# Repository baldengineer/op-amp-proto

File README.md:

## Op Amp board for Prototyping and testing Op Amps
This board characterizes op amps in an SOIC-8 breakout board. The bottom layer is solid copper. The top has copper guard bands. There are solder jumps to connect the copper pours whatever pin is GND on the SOIC.

Turns out, if you bend the leads, version 1 can fit a DIP.

The "top" and "bottom" 2.54 mm holes are intended for power rails.

## Featured on ...
See the board in action in this element14 Present's Workbench Wednesdays video on [Slew Rate versus Rise Time](https://community.element14.com/challenges-projects/element14-presents/workbenchwednesdays/w/documents/27980/workbench-wednesdays-67-slew-rate-vs-rise-time-measurements-for-op-amps "element14 Community").

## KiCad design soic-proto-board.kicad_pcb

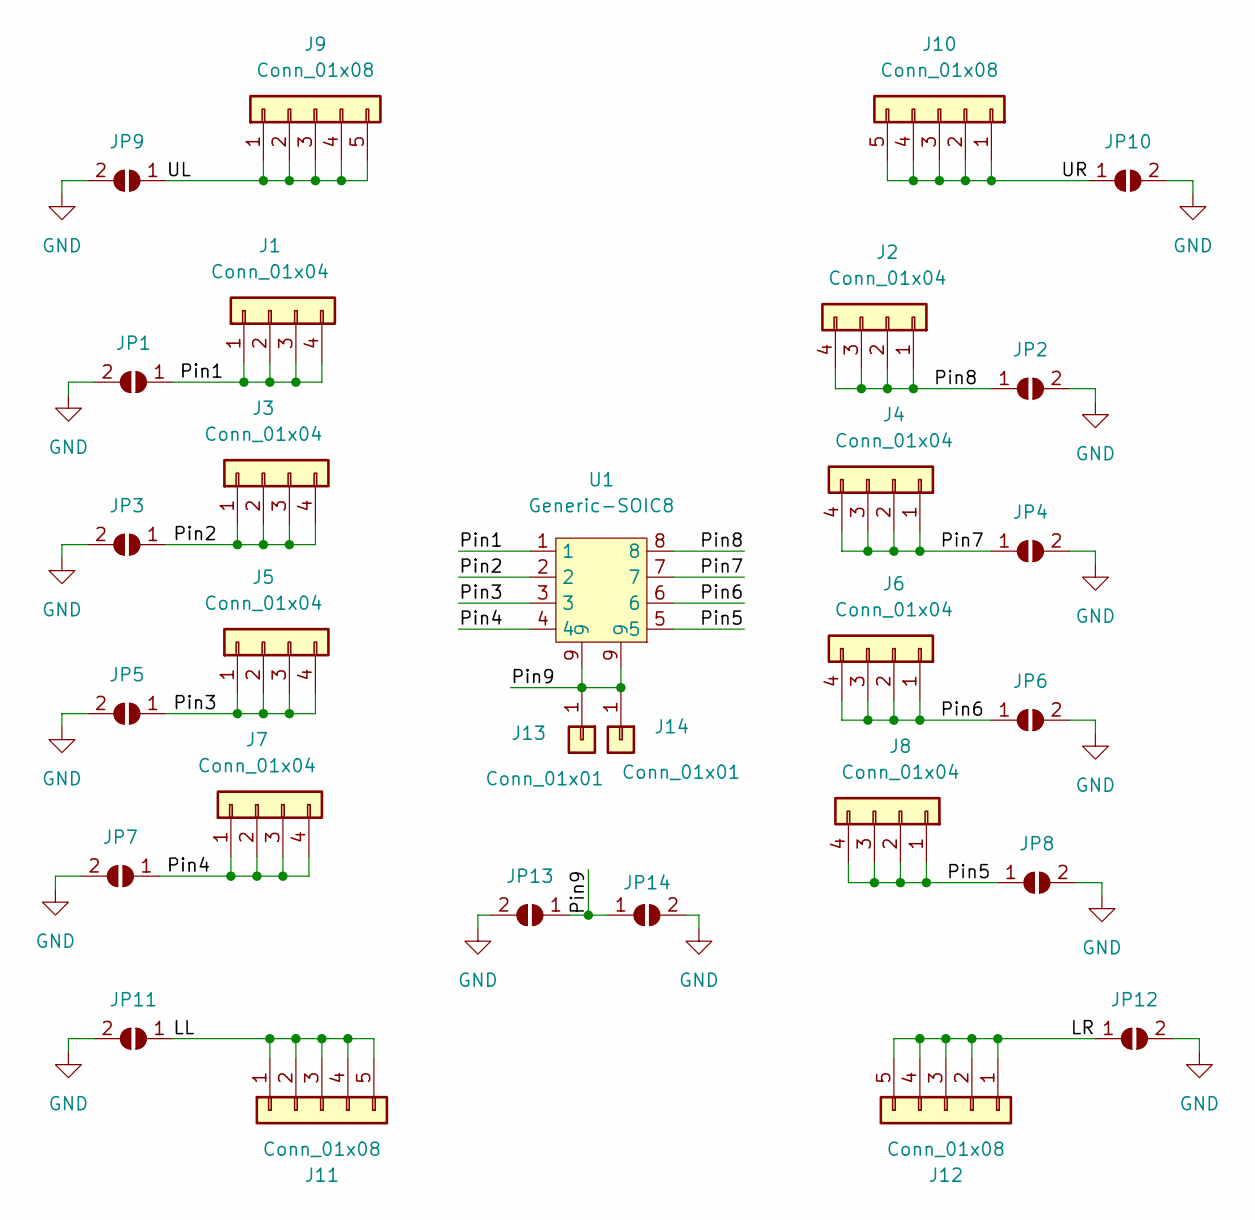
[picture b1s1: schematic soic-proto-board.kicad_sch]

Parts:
J1, J2, J3, J4, J5, J6, J7, J8: Conn_01x04; PinHeader_1x04_P2.54mm_Vertical
J9, J10, J11, J12: Conn_01x08; PinHeader_1x05_P2.54mm_Vertical
J13, J14: Conn_01x01; PinHeader_1x01_P2.54mm_Vertical
JP1, JP2, JP3, JP4, JP5, JP6, JP7, JP8, JP9, JP10, JP11, JP12, JP13, JP14: SolderJumper_2_Open; SolderJumper-2_P1.3mm_Open_RoundedPad1.0x1.5mm
U1: Generic-SOIC8; SOIC-8-1EP_3.9x4.9mm_P1.27mm_EP2.29x3mm

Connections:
/LL: J11.1, J11.2, J11.3, J11.4, J11.5, JP11.1 (A)
/LR: J12.1, J12.2, J12.3, J12.4, J12.5, JP12.1 (A)
/Pin1: J1.1, J1.2, J1.3, J1.4, JP1.1 (A), U1.1
/Pin2: J3.1, J3.2, J3.3, J3.4, JP3.1 (A), U1.2
/Pin3: J5.1, J5.2, J5.3, J5.4, JP5.1 (A), U1.3
/Pin4: J7.1, J7.2, J7.3, J7.4, JP7.1 (A), U1.4
/Pin5: J8.1, J8.2, J8.3, J8.4, JP8.1 (A), U1.5
/Pin6: J6.1, J6.2, J6.3, J6.4, JP6.1 (A), U1.6
/Pin7: J4.1, J4.2, J4.3, J4.4, JP4.1 (A), U1.7
/Pin8: J2.1, J2.2, J2.3, J2.4, JP2.1 (A), U1.8
/Pin9: J13.1, J14.1, JP13.1 (A), JP14.1 (A), U1.9
/UL: J9.1, J9.2, J9.3, J9.4, J9.5, JP9.1 (A)
/UR: J10.1, J10.2, J10.3, J10.4, J10.5, JP10.1 (A)
GND: JP1.2 (B), JP2.2 (B), JP3.2 (B), JP4.2 (B), JP5.2 (B), JP6.2 (B), JP7.2 (B), JP8.2 (B), JP9.2 (B), JP10.2 (B), JP11.2 (B), JP12.2 (B), JP13.2 (B), JP14.2 (B)

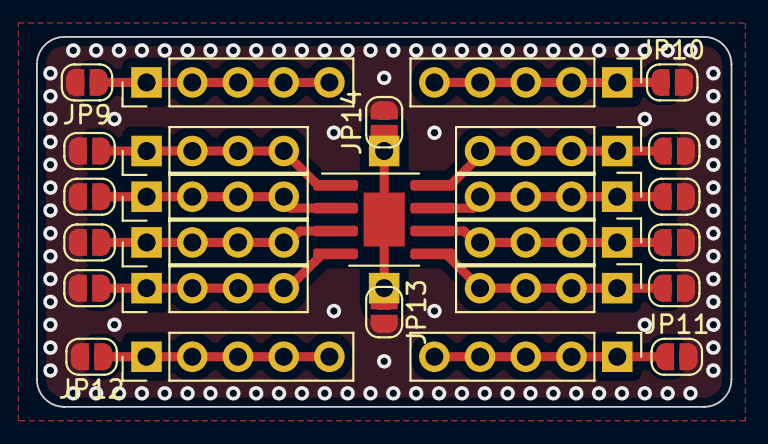
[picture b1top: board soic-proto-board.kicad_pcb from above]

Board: 2 copper layers, 38.6 x 20.6 mm, 29 parts (1 on the bottom side), 14 nets.

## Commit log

2022-12-26 ignore stuff
2022-12-26 v1 with all the flaws
2023-01-26 added yt links
